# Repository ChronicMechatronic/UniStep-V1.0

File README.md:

# UniStep-V1.0

UniStep is a simple, low-cost, translating stepper motor driver allowing you to use cheaply manufactured unipolar steppers frequently found in e-waste for any kind of CNC project like 3D printers, 
without doing the usual unipolar-to-bipolar mod needed in order to use common bipolar drivers like the A4988. 
Driving them in their original unipolar configuration makes the motors a lot quieter as current limiting relies on the internal phase resistance of the motor rather than a noisy PWM signal in constant current control.
Of course unipolar motors also have a number of disadvantages over their bipolar hybrid counterparts, (notably: lower max speeds, faster torque drop-off at high speeds, commonly low resolution of only 48 steps/revolution) making them 
indesirable for 3D printing and laser cutting (basically all direct belt drive applications). For many low-stake automation tasks they're usually sufficient though and being able to reuse e-waste is worth something as well, so this translating driver makes it easier.

Taking step/direction and enable input signals UniStep is fully compatible with the well established A4988 ecosystem, allowing to easily retrofit existing hardware.

Specifications:

-A4988 hardware compatible

-Max. voltage: 28V

-Max. current per phase: 0.5A (plenty for all unipolar motors I've so far come across)

-Microstepping mode: halfsteps (can be changed to fullsteps in software, though I'm not sure know why you'd ever do that)

Pinout diagram:

For more detailed explanations and assembly instructions watch my full video on YouTube:

Notes:
Since current is purely limited by the motor's phase resistance, the supply voltage must be matched to the motor. Otherwise overheating may occur.

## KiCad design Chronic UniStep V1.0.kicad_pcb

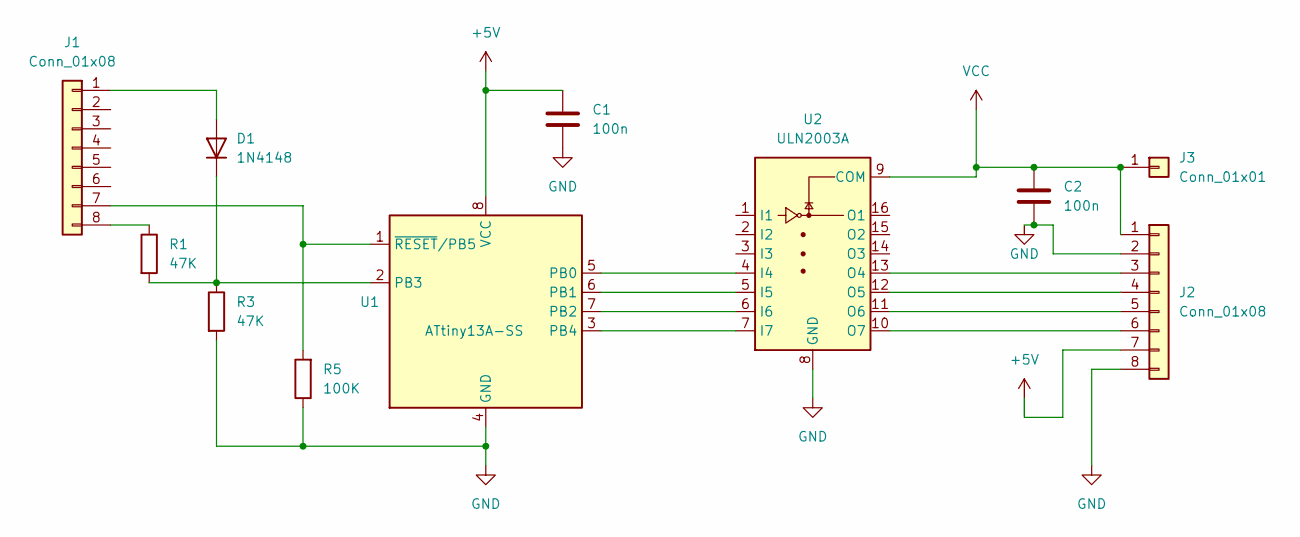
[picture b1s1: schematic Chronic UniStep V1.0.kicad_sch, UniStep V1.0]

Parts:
C1, C2: 100n; C_0603_1608Metric
D1: 1N4148; D_SOD-323
J1, J2: Conn_01x08; PinHeader_1x08_P2.54mm_Vertical
J3: Conn_01x01; PinHeader_1x01_P2.54mm_Vertical
R1, R3: 47K; R_0603_1608Metric
R5: 100K; R_0603_1608Metric
U1: ATtiny13A-SS; SOIC-8W_5.3x5.3mm_P1.27mm
U2: ULN2003A; SOIC-16_3.9x9.9mm_P1.27mm

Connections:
+5V: C1.1, J2.7, U1.8 (VCC)
GND: C1.2, C2.2, J2.2, J2.8, R3.2, R5.1, U1.4 (GND), U2.8 (GND)
unnamed: D1.1 (K), R1.2, R3.1, U1.2 (PB3)
unnamed: D1.2 (A), J1.1
unnamed: J1.7, R5.2, U1.1 (~RESET/PB5)
unnamed: J1.8, R1.1
unnamed: J2.4, U2.12 (O5)
unnamed: U1.5 (PB0), U2.4 (I4)
unnamed: U1.6 (PB1), U2.5 (I5)
unnamed: U1.7 (PB2), U2.6 (I6)
unnamed: U1.3 (PB4), U2.7 (I7)
unnamed: J2.6, U2.10 (O7)
unnamed: J2.5, U2.11 (O6)
unnamed: J2.3, U2.13 (O4)
VCC: C2.1, J2.1, J3.1, U2.9 (COM)

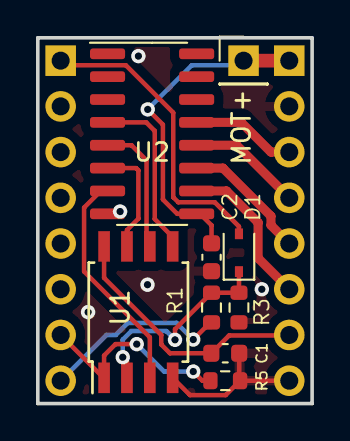
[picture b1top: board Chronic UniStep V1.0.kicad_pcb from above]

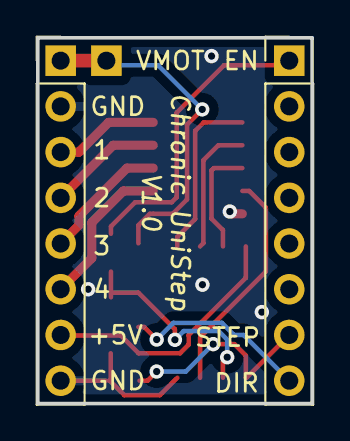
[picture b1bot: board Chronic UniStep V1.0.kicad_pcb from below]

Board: 2 copper layers, 15.2 x 20.3 mm, 11 parts (2 on the bottom side), 15 nets.

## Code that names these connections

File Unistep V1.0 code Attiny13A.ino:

/*100% functional UniStep code for Attiny13A
Distributed under the GPL-3.0 V3 license
01/28/2024 by Chronic Mechatronic
With modifications suggested by Flo (change variables to uint8/16_t; add default case to switch statement)
and tested. (Attiny can be erased and reprogrammed in-situ)

Requires following voltage divider on PB3:
47K resistor from sensepin to ground, 47K resistor from sensepin to DIR input, generic diode from ENABLE input to sensepin (cathode connects to sensepin)
*/

#include <avr/io.h>
#include <avr/interrupt.h>

//input pins:
#define StepIn PB5
#define DirEnableIn PB3

volatile bool direction = 0;   //boolean for CW or CCW rotation
volatile uint8_t StepCount = 1;   // step counter variable
uint16_t DirEnval = 0;



void setup() {

  DDRB = DDRB | B00010111; //set PB3 and PB5 as inputs, the rest as outputs using direct port manipulation

  // Enable the pin change interrupt for PB0
  PCMSK |= _BV(PCINT5);
  GIMSK |= _BV(PCIE);
  
}





void loop() {
  
  DirEnval = analogRead(DirEnableIn);   //read analog input voltage for the combined direction/enable pin

  //set direction variable true or false depending on the voltage measured on the resistor divider. True = clockwise and false = anticlockwise
  if(DirEnval<256) {direction=false;}                         //direction of rotation is CCW if measured voltage under 1.25V
  else if(DirEnval>256 && DirEnval<600) {direction=true;}     //direction of rotation is CW if voltage between 1.25V and 2.93V

  while(analogRead(DirEnableIn)>600) {           //turn motor off while enable input is high
    PORTB = B00000000;
  }

    

  switch(StepCount) {               //Main step execution. Switches PB0 through PB4 via direct port manipulation depending on the current position in the halfstep sequence
    case 1:
    PORTB = B00000001;
    break;
    
    case 2:
    PORTB = B00000011;
    break;
    
    case 3:
    PORTB = B00000010;
    break;
    
    case 4:
    PORTB = B00000110;
    break;
    
    case 5:
    PORTB = B00000100;
    break;
    
    case 6:
    PORTB = B00010100;
    break;
    
    case 7:
    PORTB = B00010000;
    break;
    
    case 8:
    PORTB = B00010001;
    break;    
  
    default:
    PORTB = B00000000;    // turn off motor in case StepCount variable doesn't match expected value
    break;
  }



} //end of void loop



ISR (PCINT0_vect) {       //interrupt service routine: counts the step sequence up or down depending on the last known state of the direction pin

if(!digitalRead(StepIn)){ /*do nothing for interrupts triggered by a falling edge*/ }
else{

  if(direction){StepCount++;}       //advance step sequence if direction CW, lower count if CCW
  else {StepCount--;}
 

  if(StepCount>8) {StepCount=1;}          //reset step counter to keep count within the 8 designated halfsteps
  else if(StepCount<1) {StepCount=8;}   
}

}

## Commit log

2024-01-28 Create LICENSE
2024-01-28 Add schematic and board files
2024-01-28 Add gerber files
2024-01-28 Add voltage LUT
2024-01-28 Add firmware
2024-01-28 Update Unistep V1.0 code Attiny13A.ino
    correct date typo
2024-01-30 Update README.md
    Add pinout diagram
2024-01-30 Update README.md
    resize pinout diagram
2024-01-30 Update README.md
    Add video link
2024-01-30 Update README.md
    trying to fix embedded video link
2024-01-30 Update README.md
    more link fixing attempts
2024-01-30 Update README.md
    trying to fix formatting
2024-01-30 Update README.md
    more formatting...
2024-01-30 Update README.md
    even more formatting
2024-01-30 Add schematic and PCB layout pics
2024-01-30 Update Unistep V1.0 code Attiny13A.ino
    Added modifications suggested by Flo
